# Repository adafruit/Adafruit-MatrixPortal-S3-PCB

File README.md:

## Adafruit Matrix Portal S3 CircuitPython Powered Internet Display PCB

<a href="http://www.adafruit.com/products/5778"><br/>
Click here to purchase one from the Adafruit shop</a>

PCB files for the Adafruit Matrix Portal S3 CircuitPython Powered Internet Display.

Format is EagleCAD schematic and board layout
* https://www.adafruit.com/product/5778

### Description

Folks love our [wide selection of RGB matrices](https://www.adafruit.com/category/327) and accessories for making custom colorful LED displays... and our RGB Matrix Shields and FeatherWings can be quickly soldered together to make the wiring much easier. But what if we made it *even easier* than that? **Like, no solder, no wiring, just instant plug-and-play?** Dream no more - with the **Adafruit Matrix Portal S3 add-on for RGB Matrices**, there's never been an easier way to create powerful Internet-connected LED displays.

You can plug directly into the back of [any HUB-75 compatible display (all the ones we stock will work) from 16x32 up to 64x64](https://www.adafruit.com/category/327) or use the stock 2x8 IDC cables to plug into the front. Use the included screws to attach the power cable to the power plugs with a common screwdriver, then power it with any USB C power supply. Chain dozens of displays for long stretches, or you can panelize them in a grid for bigger displays. For larger projects, power the matrices with a separate 5V power adapter.

Then code up your project in [CircuitPython](https://learn.adafruit.com/rgb-led-matrices-matrix-panels-with-circuitpython) or [Arduino](https://learn.adafruit.com/adafruit-protomatter-rgb-matrix-library), our Protomatter matrix library works great on the ESP32-S3 chipset, knowing that you've got the wiring and level shifting all handled. Here's what you get:

- **ESP32-S3 processor**, 8 MB flash, 2 MB of SRAM, with full Arduino or CircuitPython support
- **WiFi and Bluetooth LE** baked right in, full Arduino support. CircuitPython only supports WiFi at this time, not BLE on the S3 chip.
- **USB Type C** connector for data and power connectivity
- [**I2C STEMMA QT connector** for plug-n-play use of any of our STEMMA QT devices or sensors](https://www.adafruit.com/category/620) can also be used with [any Grove I2C devices using this adapter cable](https://www.adafruit.com/product/4528)
- **JST 3-pin connector** that also has analog input [for quick connection with any JST PH 2.0mm pitch cable](https://www.adafruit.com/search?q=jst+2mm).
- **LIS3DH accelerometer** for digital sand projects or detecting taps/orientation.
- **GPIO breakout strip -** has reset, boot selection, TX debug output, and 6 GPIO including 4 analog inputs with PWM, SPI, or I2S support for adding other hardware.
- **Address E line jumper** for use with 64x64 matrices (check your matrix to see which pin is used for address E, we default to pin 8
- **Two user interface buttons** + one reset button
- **Indicator NeoPixel** and red LED
- **Green power indicator LEDs** for both 3V and 5V power
- **2x10 socket connector** fits snugly into 2x8 HUB75 ports without worrying about 'off by one' errors
- **2x8 IDC plug connector** works with standard cables that come with matrices.

The Matrix Portal uses an Espressif ESP32-S3 Wi-Fi+BLE chipset, and has dropped the SAMD51 from the original Matrix Portal due to silicon shortages. But turns out the S3 is really great at doing all the work of the original all on its own:

- The S3 has a parallel output drive peripheral which means that controlling the matrix is done without bitbanging.
- The S3 has two cores so one can be dedicated to WiFi networking or matrix control while the other runs your code.
- With native USB, its easy to have it act like a keyboard, or mouse, or MIDI device and it also has plenty of I2C, SPI, I2S, UART and analog inputs.
- Lots of memory: 8MB of Flash means plenty of space for code, files, GIFs and more. 2MB of PSRAM means you can read and parse a lot of IoT data and still have plenty of RAM for the matrix display buffers.
- The only real thing missing from the original Matrix Portal is the S3 does not have an analog output DAC pin, we recommend an I2S amplifier for audio instead.

Comes with one fully programmed and assembled MatrixPortal, preprogrammed with a basic display demo for 32x64 LED matrices.

### License

Adafruit invests time and resources providing this open source design, please support Adafruit and open-source hardware by purchasing products from [Adafruit](https://www.adafruit.com)!

Designed by Limor Fried/Ladyada for Adafruit Industries.

Creative Commons Attribution/Share-Alike, all text above must be included in any redistribution.
See license.txt for additional details.

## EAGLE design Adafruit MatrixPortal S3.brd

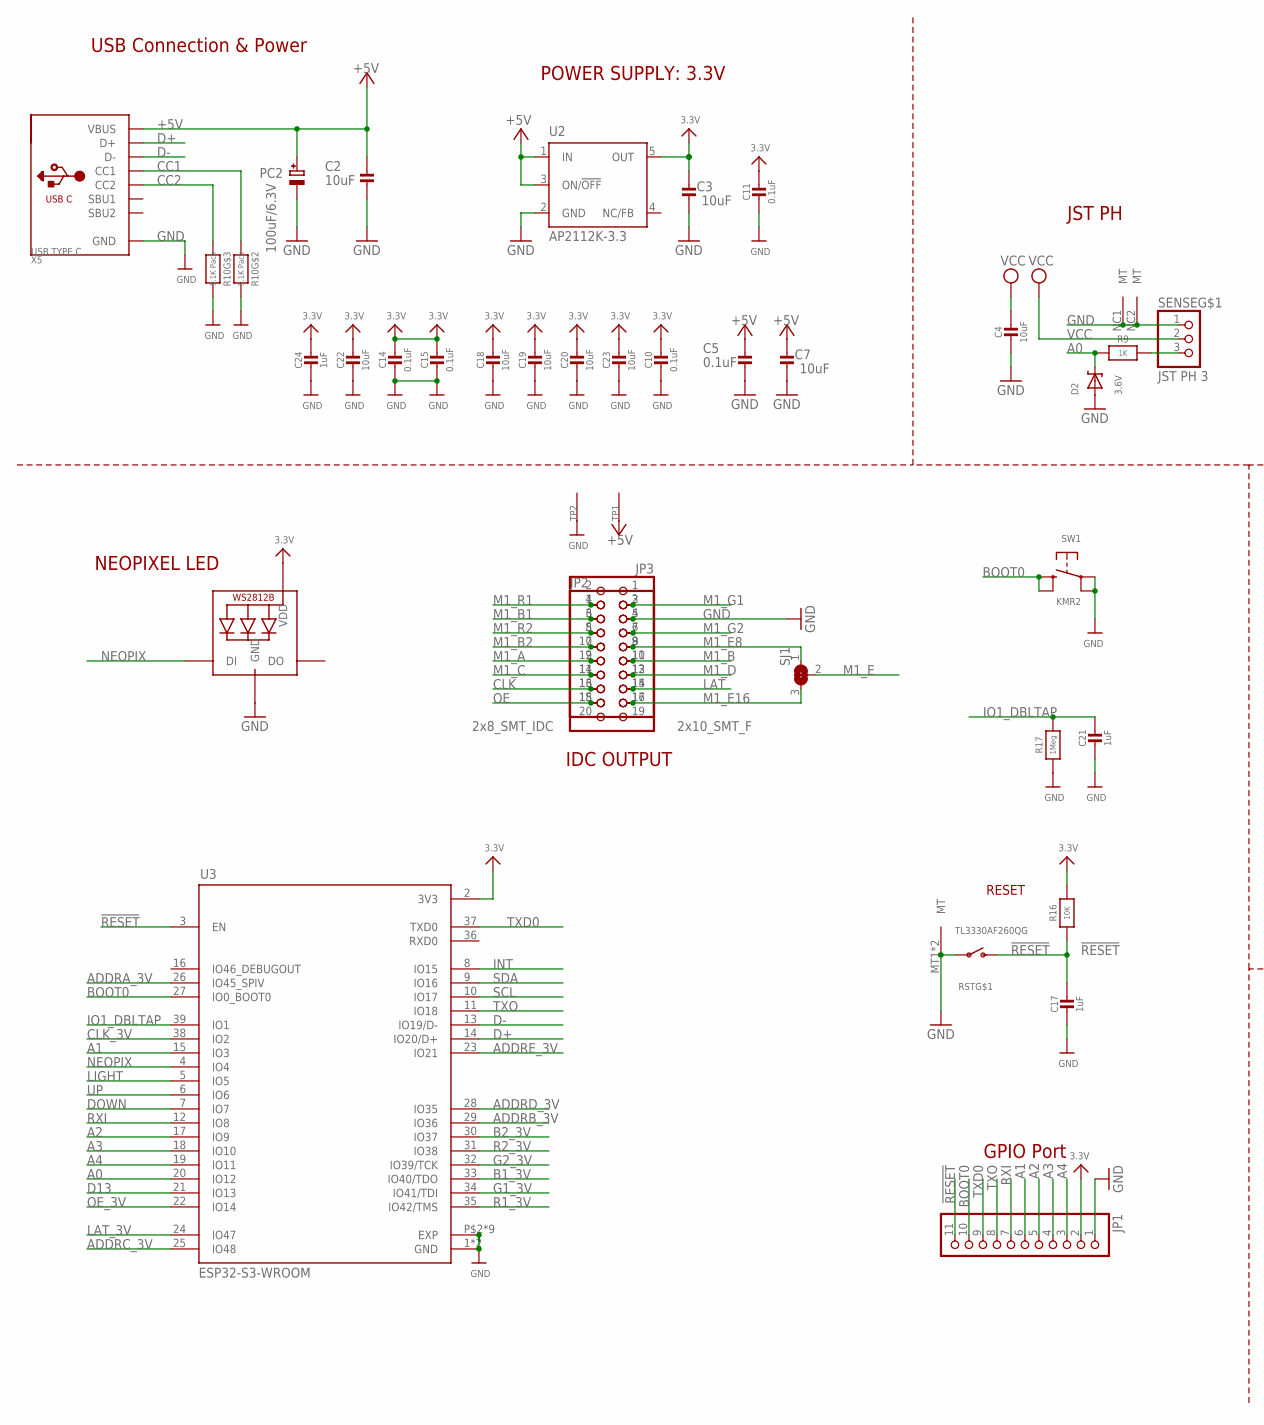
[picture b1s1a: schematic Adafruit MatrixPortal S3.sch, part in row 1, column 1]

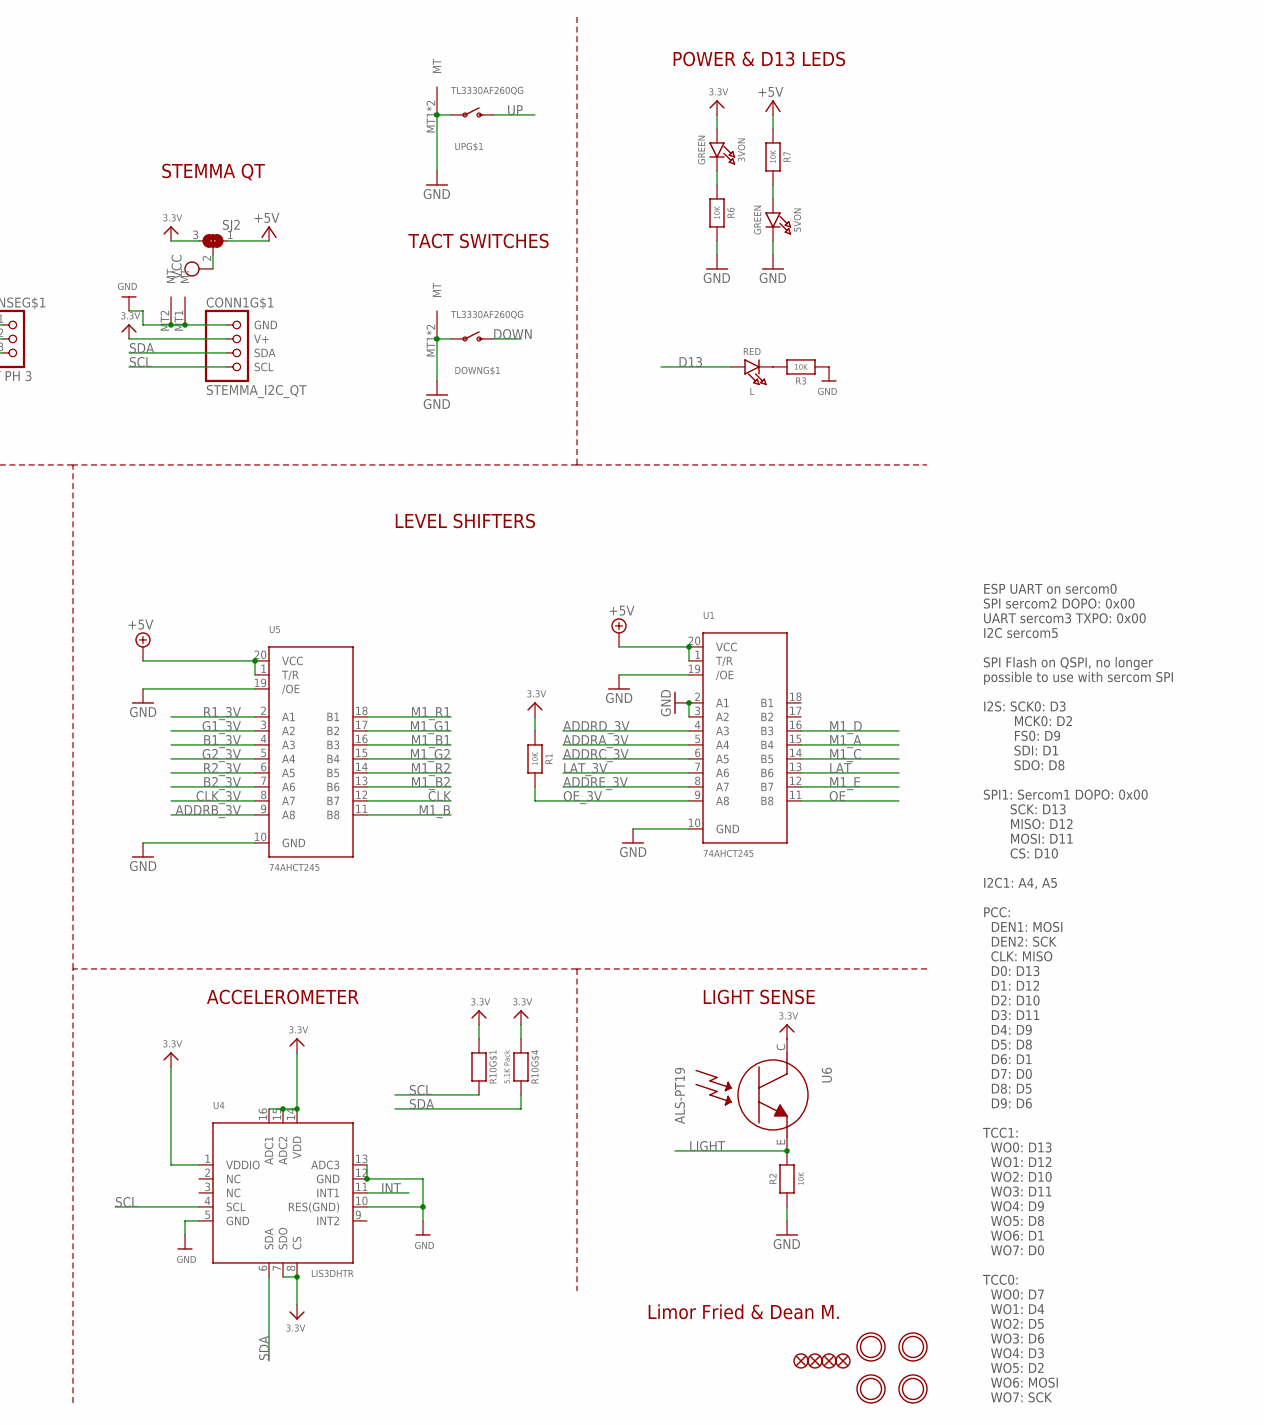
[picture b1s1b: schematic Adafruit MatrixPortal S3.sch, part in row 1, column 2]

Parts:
3VON, 5VON: GREEN; CHIPLED_0603_NOOUTLINE
C2, C3, C4, C7, C18, C19, C20, C22, C23: 10uF; 0805-NO
C5, C10, C11, C14, C15: 0.1uF; 0603-NO
C17, C21, C24: 1uF; 0603-NO
CONN1: STEMMA_I2C_QT; JST_SH4
D2: 3.6V; SOD-323
DOWN: TL3330AF260QG; SPST_TACTILE_RA
FID1, FID2, FID3, FID4: FIDUCIAL_1MM
JP1: HEADER-1X11; 1X11_ROUND
JP2: 2x8_SMT_IDC; 2X08_SHROUDEDSMT
JP3: 2x10_SMT_F; 2X10_SMT_FEMALE
L: RED; CHIPLED_0603_NOOUTLINE
LED1: WS2812B_3535FULL; LED3535_FULLPADS
PC2: 100uF/6.3V; PANASONIC_D
R1, R2, R3, R6, R7, R16: 10K; 0603-NO
R9: 1K; 0603-NO
R10: 5.1K Pack; RESPACK_4X0603
R17: 1Meg; 0603-NO
RST: TL3330AF260QG; SPST_TACTILE_RA
SENSE: JST PH 3; JSTPH3
SJ1, SJ2: SOLDERJUMPER_2WAY; SOLDERJUMPER_2WAY_OPEN_NOPASTE
SW1: KMR2; BTN_RKB2_4.6X2.8
TP1, TP2: SEWTAP_SMTNUTM3; SMT_NUT_3MM
U1, U5: 74AHCT245; TSSOP20
U2: AP2112K-3.3; SOT23-DBV
U3: ESP32-S3-WROOM; S3-WROOM32
U4: LIS3DHTR; LGA16_3X3MM
U6: ALS-PT19; ALS-PT19-315C
U$14, U$19, U$22, U$24: MOUNTINGHOLE2.5; MOUNTINGHOLE_2.5_PLATED
UP: TL3330AF260QG; SPST_TACTILE_RA
X5: USB TYPE C; USB_C_CUSB31-CFM2AX-01-X

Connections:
3.3V: 3VON.A, C3.2, C10.2, C11.2, C14.2, C15.2, C18.1, C19.1, C20.1, C22.1, C23.1, C24.1, CONN1.2 (V+), JP1.2, LED1.2 (VDD), R1.1, R10.1, R10.4 (1), R16.2, SJ2.3, U2.5 (OUT), U3.2 (3V3), U4.1 (VDDIO), U4.7 (SDO), U4.8 (CS), U4.14 (VDD), U4.15 (ADC2), U4.16 (ADC1), U6.C
!RESET: C17.1, JP1.11, R16.1, RST.2 (S), U3.3 (EN)
+5V: C2.2, C5.2, C7.2, PC2.+, R7.1, SJ2.1, TP1.P$1, U1.1 (T/R), U1.20 (VCC), U2.1 (IN), U2.3 (ON/!OFF), U5.1 (T/R), U5.20 (VCC), X5.A4B9 (VBUS), X5.B4A9 (VBUS)
A0: D2.C, R9.2, U3.20 (IO12)
A0_JST: R9.1, SENSE.3
A1: JP1.6, U3.15 (IO3)
A2: JP1.5, U3.17 (IO9)
A3: JP1.4, U3.18 (IO10)
A4: JP1.3, U3.19 (IO11)
ADDRA_3V: U1.5 (A4), U3.26 (IO45_SPIV)
ADDRB_3V: U3.29 (IO36), U5.9 (A8)
ADDRC_3V: U1.6 (A5), U3.25 (IO48)
ADDRD_3V: U1.4 (A3), U3.28 (IO35)
ADDRE_3V: U1.8 (A7), U3.23 (IO21)
B1_3V: U3.33 (IO40/TDO), U5.4 (A3)
B2_3V: U3.30 (IO37), U5.7 (A6)
BOOT0: JP1.10, SW1.B (S), SW1.B' (S1), U3.27 (IO0_BOOT0)
CC1: R10.2 (1), X5.A5 (CC1)
CC2: R10.3 (1), X5.B5 (CC2)
CLK: JP2.13, JP3.16, U5.12 (B7)
CLK_3V: U3.38 (IO2), U5.8 (A7)
D13: L.A, U3.21 (IO13)
D+: U3.14 (IO20/D+), X5.A6 (D+), X5.B6 (D+)
D-: U3.13 (IO19/D-), X5.A7 (D-), X5.B7 (D-)
DOWN: DOWN.2 (S), U3.7 (IO7)
G1_3V: U3.34 (IO41/TDI), U5.3 (A2)
G2_3V: U3.32 (IO39/TCK), U5.5 (A4)
GND: 5VON.C, C2.1, C3.1, C4.2, C5.1, C7.1, C10.1, C11.1, C14.1, C15.1, C17.2, C18.2, C19.2, C20.2, C21.2, C22.2, C23.2, C24.2, CONN1.1 (GND), CONN1.MT1 (MT), CONN1.MT2 (MT), D2.A, DOWN.1, DOWN.MT1 (MT), DOWN.MT2 (MT), JP1.1, JP2.4, JP3.5, LED1.4 (GND), PC2.-, R2.2, R3.2, R6.2, R10.6 (2), R10.7 (2), R17.1, RST.1, RST.MT1 (MT), RST.MT2 (MT), SENSE.1, SENSE.NC1 (MT), SENSE.NC2 (MT), SW1.A, SW1.A' (P1), TP2.P$1, U1.2 (A1), U1.3 (A2), U1.10 (GND), U1.19 (/OE), U2.2 (GND), U3.1 (GND), U3.40 (GND), U3.P$2 (EXP), U3.P$3 (EXP), U3.P$4 (EXP), U3.P$5 (EXP), U3.P$6 (EXP), U3.P$7 (EXP), U3.P$8 (EXP), U3.P$9 (EXP), U3.P$10 (EXP), U4.5 (GND), U4.10 (RES(GND)), U4.12 (GND), U4.13 (ADC3), U5.10 (GND), U5.19 (/OE), UP.1, UP.MT1 (MT), UP.MT2 (MT), X5.A1B12 (GND), X5.B1A12 (GND)
INT: U3.8 (IO15), U4.11 (INT1)
IO1_DBLTAP: C21.1, R17.2, U3.39 (IO1)
LAT: JP2.14, JP3.15, U1.13 (B6)
LAT_3V: U1.7 (A6), U3.24 (IO47)
LIGHT: R2.1, U3.5 (IO5), U6.E
M1_A: JP2.9, JP3.12, U1.15 (B4)
M1_B: JP2.10, JP3.11, U5.11 (B8)
M1_B1: JP2.3, JP3.6, U5.16 (B3)
M1_B2: JP2.7, JP3.10, U5.13 (B6)
M1_C: JP2.11, JP3.14, U1.14 (B5)
M1_D: JP2.12, JP3.13, U1.16 (B3)
M1_E: SJ1.2, U1.12 (B7)
M1_E8: JP2.8, JP3.9, SJ1.1
M1_E16: JP2.16, JP3.17, SJ1.3
M1_G1: JP2.2, JP3.3, U5.17 (B2)
M1_G2: JP2.6, JP3.7, U5.15 (B4)
M1_R1: JP2.1, JP3.4, U5.18 (B1)
M1_R2: JP2.5, JP3.8, U5.14 (B5)
unnamed: 5VON.A, R7.2
unnamed: 3VON.C, R6.1
unnamed: L.C, R3.1
NEOPIX: LED1.1 (DI), U3.4 (IO4)
OE: JP2.15, JP3.18, U1.11 (B8)
OE_3V: R1.2, U1.9 (A8), U3.22 (IO14)
R1_3V: U3.35 (IO42/TMS), U5.2 (A1)
R2_3V: U3.31 (IO38), U5.6 (A5)
RXI: JP1.7, U3.12 (IO8)
SCL: CONN1.4 (SCL), R10.8 (2), U3.10 (IO17), U4.4 (SCL)
SDA: CONN1.3 (SDA), R10.5 (2), U3.9 (IO16), U4.6 (SDA)
TXD0: JP1.9, U3.37 (TXD0)
TXO: JP1.8, U3.11 (IO18)
UP: U3.6 (IO6), UP.2 (S)
VCC: C4.1, SENSE.2, SJ2.2

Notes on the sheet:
Limor Fried & Dean M.
USB Connection & Power
POWER SUPPLY: 3.3V
POWER & D13 LEDS
NEOPIXEL LED
GPIO Port
ESP UART on sercom0 SPI sercom2 DOPO: 0x00 UART sercom3 TXPO: 0x00 I2C sercom5 SPI Flash on QSPI, no longer possible to use with sercom SPI I2S: SCK0: D3 MCK0: D2 FS0: D9 SDI: D1 SDO: D8 SPI1: Sercom1 DOPO: 0x00 SCK: D13 MISO: D12 MOSI: D11 CS: D10 I2C1: A4, A5 PCC: DEN1: MOSI DEN2: SCK CLK: MISO D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
RESET
JST PH
STEMMA QT
TACT SWITCHES
LEVEL SHIFTERS
ACCELEROMETER
LIGHT SENSE
IDC OUTPUT

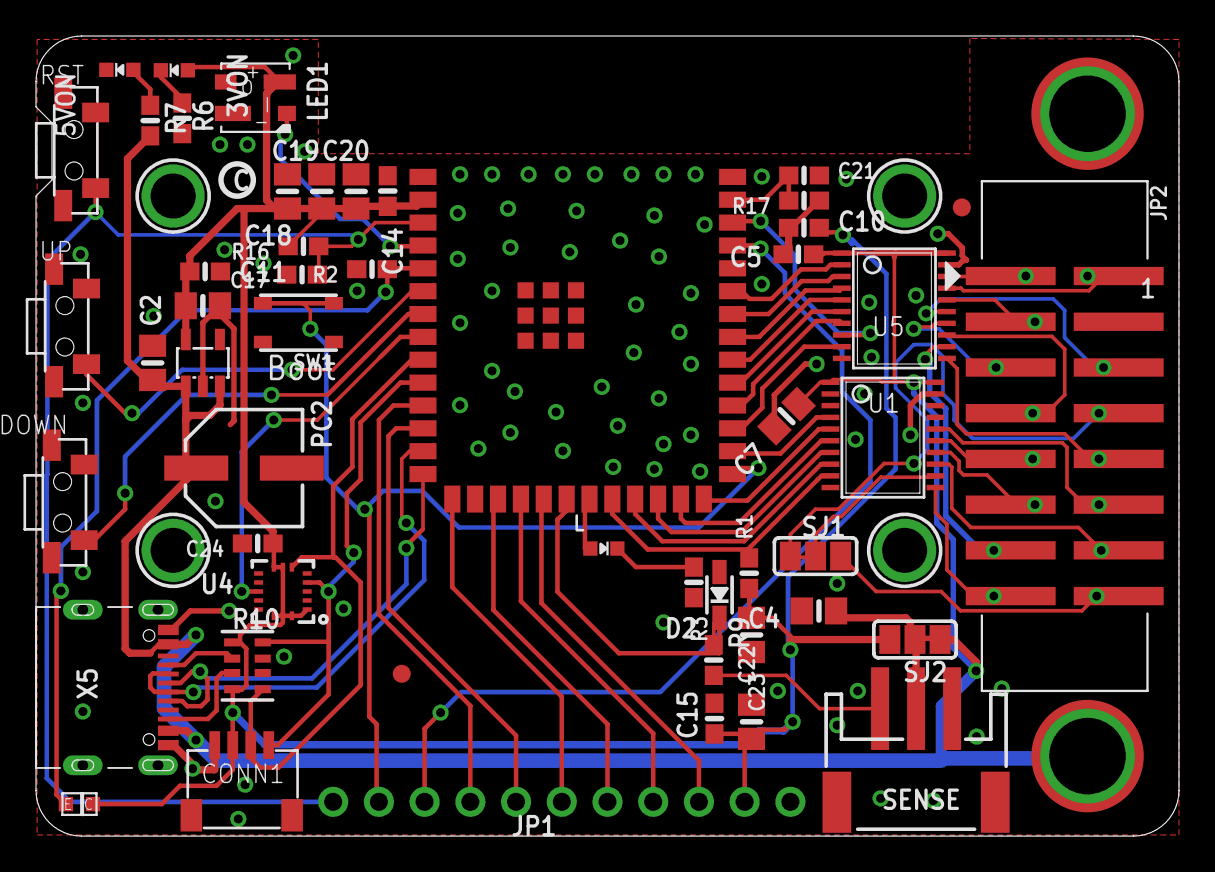
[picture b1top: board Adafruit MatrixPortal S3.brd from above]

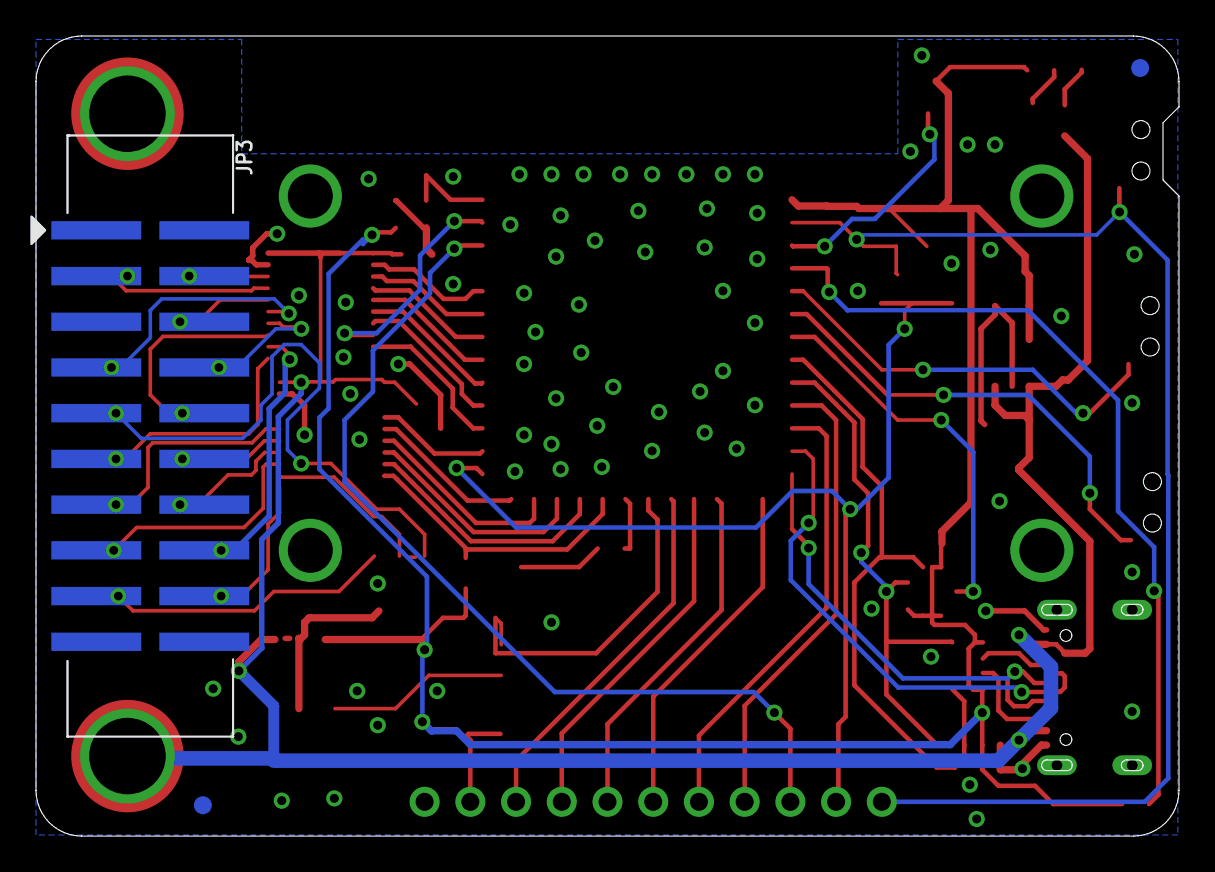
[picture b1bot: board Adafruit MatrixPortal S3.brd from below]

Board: 2 copper layers, 63.5 x 44.5 mm, 63 parts (4 on the bottom side), 61 nets.

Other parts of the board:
U$25: S3_MATRIXPORTAL_TOP
U$26: S3_MATRIXPORTAL_BOT
U$44: PCBFEAT-REV-040

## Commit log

2023-07-18 Add PCB Files
2023-07-18 fix readme
2023-07-18 Remove ignored file
2023-07-18 Add git ignore file
2023-07-18 Add Factory Reset UF2
2023-07-18 Add Factory Reset bin and move both into correct folder
2023-08-10 Update factory reset images
2023-08-16 Updated Board with more dimensions

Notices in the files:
parts and their libraries:
microbuilder: This work is placed in the public domain, and may be freely used for commercial and non-commercial work with the following conditions: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
SparkFun-Aesthetics: Licensing: CC v3.0 Share-Alike You are welcome to use this library for commercial purposes.
